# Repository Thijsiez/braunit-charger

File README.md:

# braunit-charger

## :construction: WIP :construction:
This repo is currently a work-in-progress. I will add more information and documentation when the design of the charger is done.  
As long as this message is here, I'm open to suggestions but please do not assume anything is done or will work without issues.

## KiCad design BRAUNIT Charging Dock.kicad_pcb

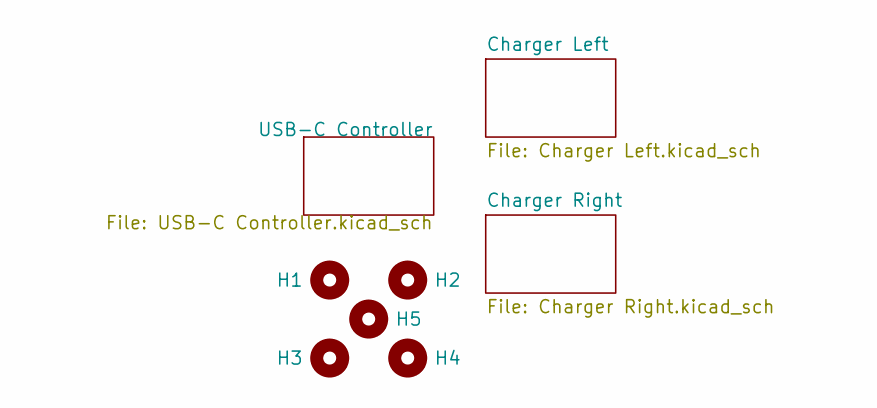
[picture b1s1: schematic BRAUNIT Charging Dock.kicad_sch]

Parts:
H1, H2, H3, H4, H5: MountingHole; MountingHole_2.7mm_M2.5_DIN912_Keepout

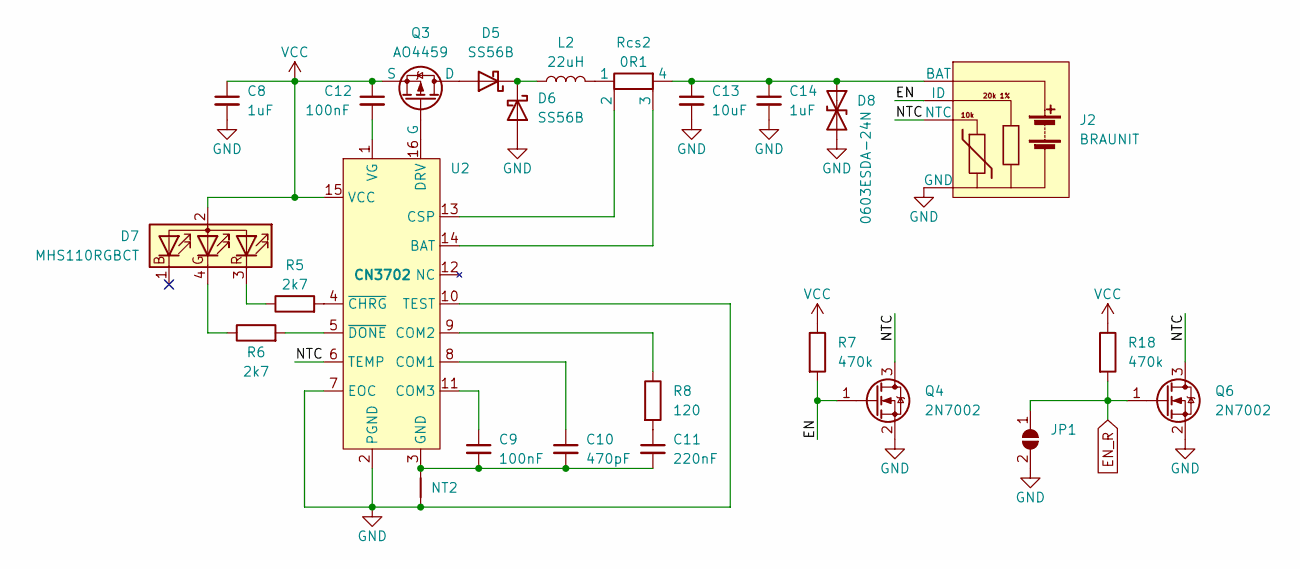
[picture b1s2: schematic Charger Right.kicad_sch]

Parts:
C8, C14: 1uF; C_0805_2012Metric; LCSC C91185
C9, C12: 100nF; C_0603_1608Metric; LCSC C14663
C10: 470pF; C_0603_1608Metric; LCSC C107092
C11: 220nF; C_0603_1608Metric; LCSC C107083
C13: 10uF; C_1206_3216Metric; LCSC C109464
D5, D6: SS56B; D_SMB; LCSC C382814
D7: MHS110RGBCT; LED_RGB_Meihua_MHS110RGBCT; LCSC C389528
D8: 0603ESDA-24N; D_0603_1608Metric; LCSC C316056
J2: BRAUNIT; Blade_1x04_P2.5mm_Vertical_BRAUNIT_Loose
JP1: SolderJumper_2_Open; SolderJumper-2_P1.3mm_Open_TrianglePad1.0x1.5mm
L2: 22uH; L_Sunltech_SLO0630H; LCSC C207843
NT2: NetTie_2; NetTie-2_SMD_Pad0.5mm
Q3: AO4459; SOIC-8_3.9x4.9mm_P1.27mm; LCSC C49047
Q4, Q6: 2N7002; SOT-23; LCSC C8545
R5, R6: 2k7; R_0603_1608Metric; LCSC C114612
R7, R18: 470k; R_0603_1608Metric; LCSC C114622
R8: 120; R_0603_1608Metric; LCSC C114640
Rcs2: 0R1; R_Shunt_2010_5025Metric; LCSC C309644
U2: CN3702; TSSOP-16_4.4x5mm_P0.65mm; LCSC C40655

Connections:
/Charger Right/EN: J2.2 (ID), Q4.1 (G), R7.2
/Charger Right/NTC: J2.3 (NTC), Q4.3 (D), Q6.3 (D), U2.6 (TEMP)
EN_R: JP1.1 (A), Q6.1 (G), R18.2; also elsewhere on the board
GND: C8.2, C13.2, C14.2, D6.2 (A), D8.2 (A2), J2.4 (GND), JP1.2 (B), NT2.2, Q4.2 (S), Q6.2 (S), U2.2 (PGND), U2.7 (EOC), U2.10 (TEST); also elsewhere on the board
unnamed: C9.1, U2.11 (COM3)
unnamed: C10.1, U2.8 (COM1)
unnamed: C9.2, C10.2, C11.2, NT2.1, U2.3 (GND)
unnamed: C11.1, R8.2
unnamed: C12.2, U2.1 (VG)
unnamed: C13.1, C14.1, D8.1 (A1), J2.1 (BAT), Rcs2.4
unnamed: D5.1 (K), D6.1 (K), L2.1
unnamed: D5.2 (A), Q3.5 (D), Q3.6 (D), Q3.7 (D), Q3.8 (D)
unnamed: D7.3 (RK), R5.1
unnamed: D7.4 (GK), R6.1
unnamed: L2.2, Rcs2.1
unnamed: Q3.4 (G), U2.16 (DRV)
unnamed: R5.2, U2.4 (~CHRG)
unnamed: R6.2, U2.5 (~DONE)
unnamed: R8.1, U2.9 (COM2)
unnamed: Rcs2.2, U2.13 (CSP)
unnamed: Rcs2.3, U2.14 (BAT)
VCC: C8.1, C12.1, D7.2 (A), Q3.1 (S), Q3.2 (S), Q3.3 (S), R7.1, R18.1, U2.15 (VCC); also elsewhere on the board

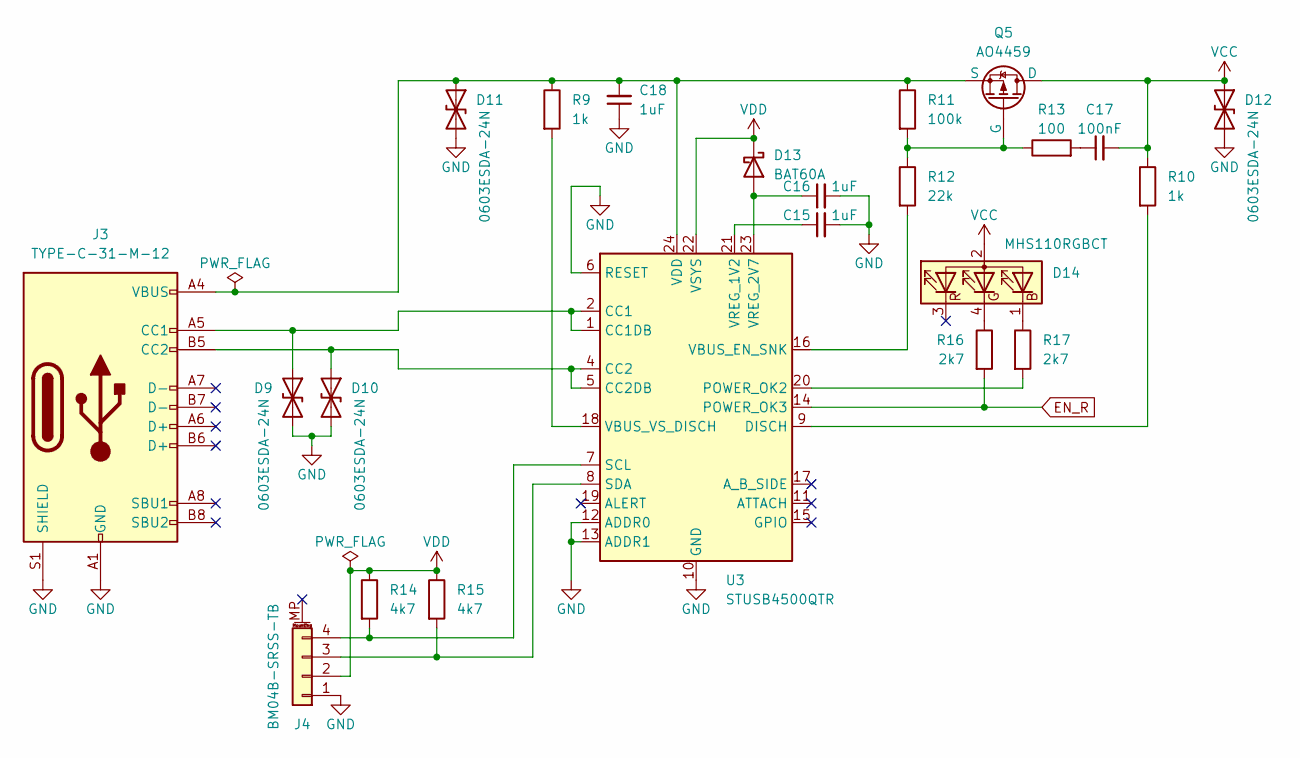
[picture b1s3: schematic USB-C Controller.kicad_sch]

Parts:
C15, C16, C18: 1uF; C_0805_2012Metric; LCSC C91185
C17: 100nF; C_0603_1608Metric; LCSC C14663
D9, D10, D11, D12: 0603ESDA-24N; D_0603_1608Metric; LCSC C316056
D13: BAT60A; D_SOD-323; LCSC C117485
D14: MHS110RGBCT; LED_RGB_Meihua_MHS110RGBCT; LCSC C389528
J3: TYPE-C-31-M-12; USB_C_Receptacle_HRO_TYPE-C-31-M-12; LCSC C165948
J4: BM04B-SRSS-TB; JST_SH_BM04B-SRSS-TB_1x04-1MP_P1.00mm_Vertical; LCSC C160390
Q5: AO4459; SOIC-8_3.9x4.9mm_P1.27mm; LCSC C49047
R9, R10: 1k; R_0603_1608Metric; LCSC C22548
R11: 100k; R_0603_1608Metric; LCSC C14675
R12: 22k; R_0603_1608Metric; LCSC C114065
R13: 100; R_0603_1608Metric; LCSC C105588
R14, R15: 4k7; R_0603_1608Metric; LCSC C99782
R16, R17: 2k7; R_0603_1608Metric; LCSC C114612
U3: STUSB4500QTR; QFN-24-1EP_4x4mm_P0.5mm_EP2.7x2.7mm; LCSC C2678061

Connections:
EN_R: R16.2, U3.14 (POWER_OK3); also elsewhere on the board
GND: C15.2, C16.2, C18.1, D9.2 (A2), D10.2 (A2), D11.2 (A2), D12.2 (A2), J3.A1 (GND), J3.A12 (GND), J3.B1 (GND), J3.B12 (GND), J3.S1 (SHIELD), J4.1, U3.6 (RESET), U3.10 (GND), U3.12 (ADDR0), U3.13 (ADDR1), U3.25 (GND); also elsewhere on the board
unnamed: C15.1, U3.21 (VREG_1V2)
unnamed: C16.1, D13.2 (A), U3.23 (VREG_2V7)
unnamed: C17.1, R13.2
unnamed: C18.2, D11.1 (A1), J3.A4 (VBUS), J3.A9 (VBUS), J3.B4 (VBUS), J3.B9 (VBUS), Q5.1 (S), Q5.2 (S), Q5.3 (S), R9.1, R11.1, U3.24 (VDD)
unnamed 30: D9.1 (A1), J3.A5 (CC1), U3.1 (CC1DB), U3.2 (CC1); also elsewhere on the board
unnamed: D10.1 (A1), J3.B5 (CC2), U3.4 (CC2), U3.5 (CC2DB)
unnamed: D14.1 (BK), R17.1
unnamed: D14.4 (GK), R16.1
unnamed: J4.3, R15.2, U3.8 (SDA)
unnamed: J4.4, R14.2, U3.7 (SCL)
unnamed 40: Q5.4 (G), R11.2, R12.1, R13.1; also elsewhere on the board
unnamed: R9.2, U3.18 (VBUS_VS_DISCH)
unnamed: R10.2, U3.9 (DISCH)
unnamed 49: R12.2, U3.16 (VBUS_EN_SNK); also elsewhere on the board
unnamed: R17.2, U3.20 (POWER_OK2)
VCC: C17.2, D12.1 (A1), D14.2 (A), Q5.5 (D), Q5.6 (D), Q5.7 (D), Q5.8 (D), R10.1; also elsewhere on the board
VDD: D13.1 (K), J4.2, R14.1, R15.1, U3.22 (VSYS)

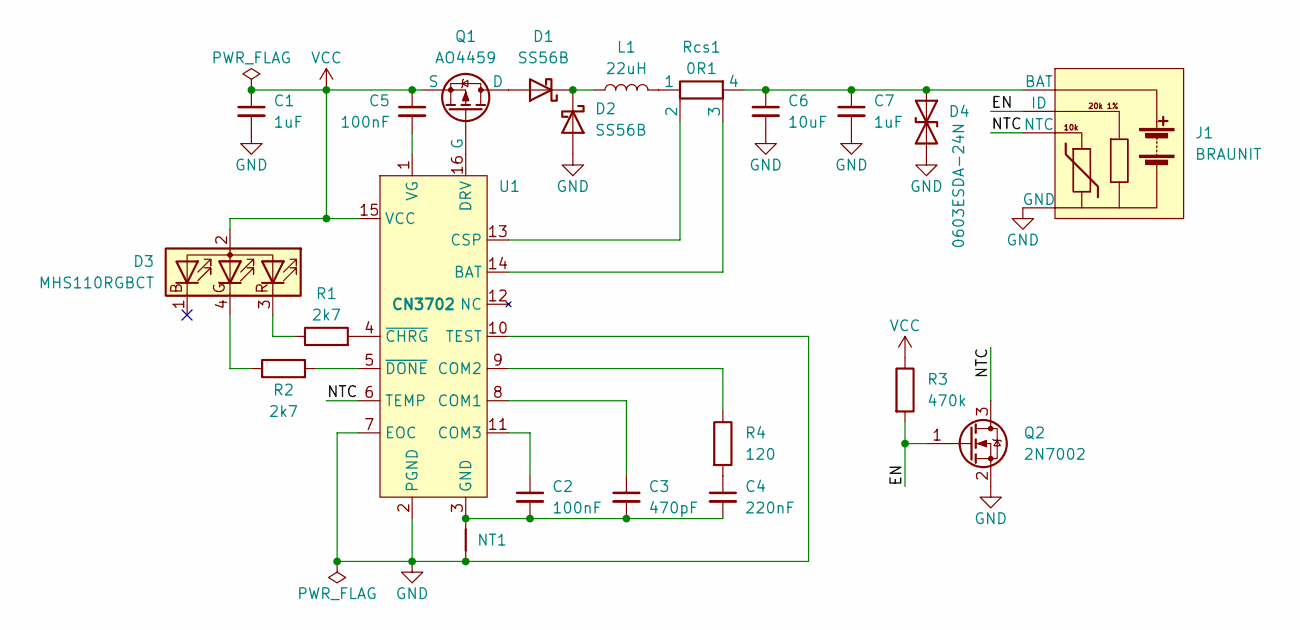
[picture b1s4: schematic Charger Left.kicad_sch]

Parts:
C1, C7: 1uF; C_0805_2012Metric; LCSC C91185
C2, C5: 100nF; C_0603_1608Metric; LCSC C14663
C3: 470pF; C_0603_1608Metric; LCSC C107092
C4: 220nF; C_0603_1608Metric; LCSC C107083
C6: 10uF; C_1206_3216Metric; LCSC C109464
D1, D2: SS56B; D_SMB; LCSC C382814
D3: MHS110RGBCT; LED_RGB_Meihua_MHS110RGBCT; LCSC C389528
D4: 0603ESDA-24N; D_0603_1608Metric; LCSC C316056
J1: BRAUNIT; Blade_1x04_P2.5mm_Vertical_BRAUNIT_Loose
L1: 22uH; L_Sunltech_SLO0630H; LCSC C207843
NT1: NetTie_2; NetTie-2_SMD_Pad0.5mm
Q1: AO4459; SOIC-8_3.9x4.9mm_P1.27mm; LCSC C49047
Q2: 2N7002; SOT-23; LCSC C8545
R1, R2: 2k7; R_0603_1608Metric; LCSC C114612
R3: 470k; R_0603_1608Metric; LCSC C114622
R4: 120; R_0603_1608Metric; LCSC C114640
Rcs1: 0R1; R_Shunt_2010_5025Metric; LCSC C309644
U1: CN3702; TSSOP-16_4.4x5mm_P0.65mm; LCSC C40655

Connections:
/Charger Left/EN: J1.2 (ID), Q2.1 (G), R3.2
/Charger Left/NTC: J1.3 (NTC), Q2.3 (D), U1.6 (TEMP)
GND: C1.2, C6.2, C7.2, D2.2 (A), D4.2 (A2), J1.4 (GND), NT1.2, Q2.2 (S), U1.2 (PGND), U1.7 (EOC), U1.10 (TEST); also elsewhere on the board
unnamed: C2.1, U1.11 (COM3)
unnamed: C2.2, C3.2, C4.2, NT1.1, U1.3 (GND)
unnamed: C3.1, U1.8 (COM1)
unnamed: C4.1, R4.2
unnamed: C5.2, U1.1 (VG)
unnamed: C6.1, C7.1, D4.1 (A1), J1.1 (BAT), Rcs1.4
unnamed: D1.1 (K), D2.1 (K), L1.1
unnamed: D1.2 (A), Q1.5 (D), Q1.6 (D), Q1.7 (D), Q1.8 (D)
unnamed: D3.3 (RK), R1.1
unnamed: D3.4 (GK), R2.1
unnamed: L1.2, Rcs1.1
unnamed: Q1.4 (G), U1.16 (DRV)
unnamed: R1.2, U1.4 (~CHRG)
unnamed: R2.2, U1.5 (~DONE)
unnamed: R4.1, U1.9 (COM2)
unnamed: Rcs1.2, U1.13 (CSP)
unnamed: Rcs1.3, U1.14 (BAT)
VCC: C1.1, C5.1, D3.2 (A), Q1.1 (S), Q1.2 (S), Q1.3 (S), R3.1, U1.15 (VCC); also elsewhere on the board

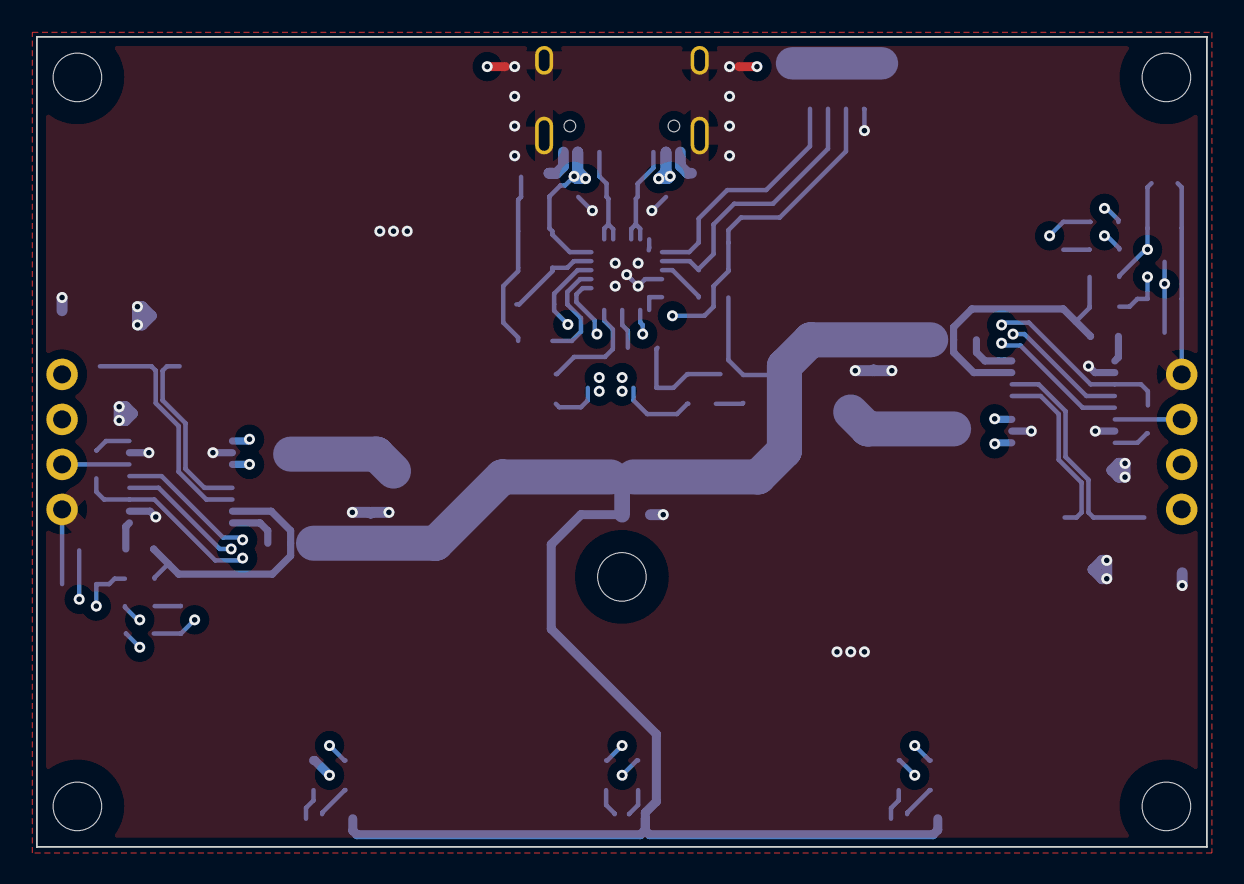
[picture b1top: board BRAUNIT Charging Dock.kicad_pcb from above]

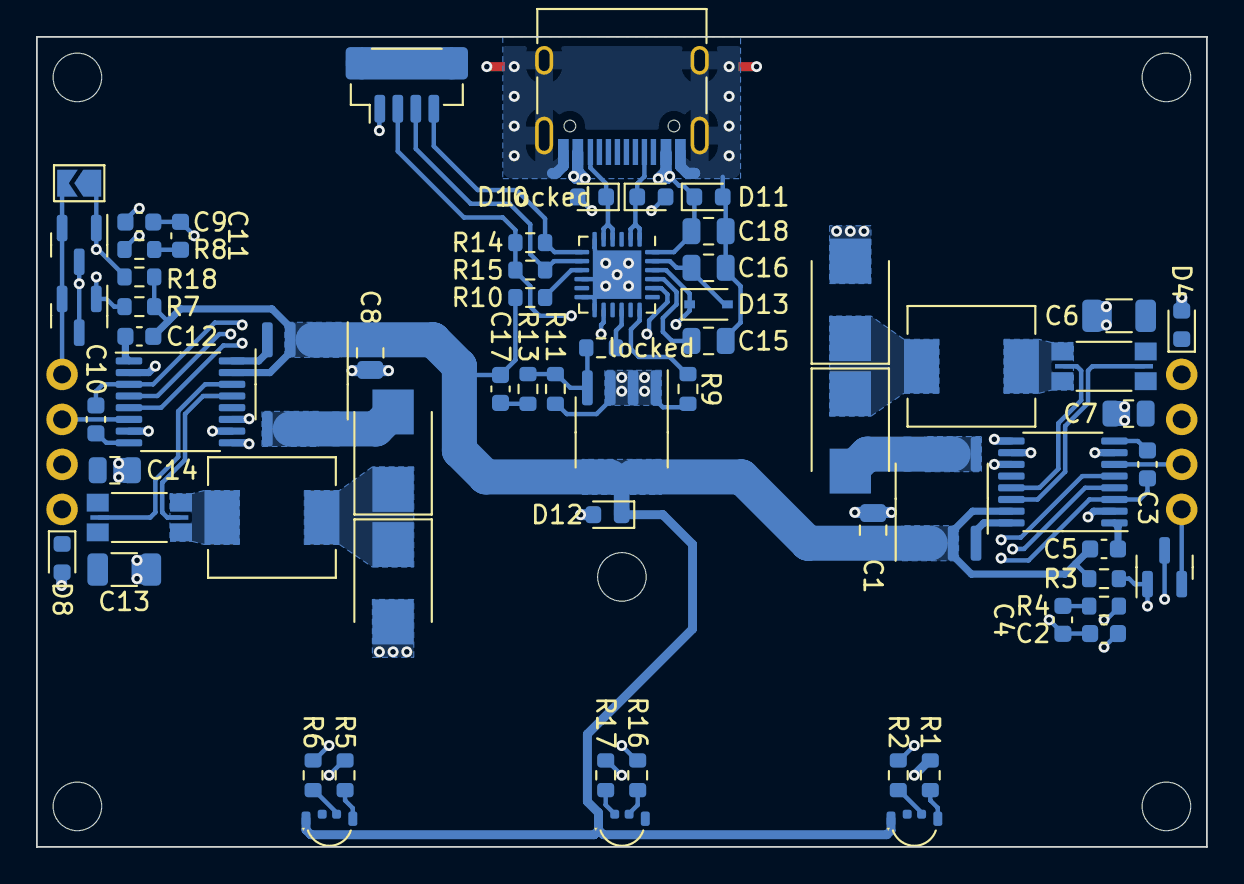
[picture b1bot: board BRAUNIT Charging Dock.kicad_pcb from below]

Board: 4 copper layers, 65.0 x 45.0 mm, 75 parts (66 on the bottom side), 57 nets.

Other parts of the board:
locked: 0603ESDA-24N; D_0603_1608Metric
locked#2: 22k; R_0603_1608Metric

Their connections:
GND: locked.2 (A2); also elsewhere on the board
unnamed 30: locked.1 (A1); also elsewhere on the board
unnamed 40: locked#2.1; also elsewhere on the board
unnamed 49: locked#2.2; also elsewhere on the board

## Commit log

2022-04-19 :tada: Lets do this!
2022-04-29 Specify LED, resistors, and start on USB-C circuit
2022-04-29 Add USB-C circuit components
2022-04-29 Add some resistors and caps
2022-04-29 Add status indicator LED
2022-04-29 Move project from Dropbox to GitHub
2022-04-29 Add LCSC part numbers for most components
2022-04-29 Add BRAUNIT connector and battery detect/charge enable
2022-05-01 Add ESD protection, I2C header, and specify passives
2022-05-02 Add USB-C status indicator LED and right charger enable
2022-05-02 Replace USB-C connector with USB 2.0 version
2022-05-02 Replace JST SH connector symbol with Mounting Pin version
2022-05-28 Initial board layout
2022-06-03 WIP traces
2022-06-15 Change to 4-layer board and do some routing
2022-08-03 Only output connections to go :)
2023-01-16 Add WIP notice
